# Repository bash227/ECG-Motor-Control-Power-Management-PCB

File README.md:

# ECG-Integrated Motor Control PCB  
**Final Project for BME405 - Introduction to Design of Medical Electronic Devices**  
*Ankara University, Department of Biomedical Engineering*  

---

## Project Overview  
A multi-functional PCB combining:  
- **ECG Signal Acquisition** (INA188 instrumentation amplifier, 0.5Hz-100Hz bandwidth)  
- **Power Management** (3.6V Li-ion charging, ±5V/12V regulation)  
- **Motor/Actuator Control** (BD6220F-E2 driver, relay circuits)  

---

## Team Members  
| Name              | Role                                  |  
|-------------------|---------------------------------------|  
| [bash227](https://github.com/bash227)| PCB Layout              |  
| [UmutAygun](https://github.com/UmutAygun)| Schematic Design          |  

---

## Repository Structure  
```plaintext
ECG_Motor_PCB/
├── Hardware/ 
│   │   
│   ├── Outputs/
│   └── 3D models/
├── Documentation/
└── README.md
```

## Key Features
### Power managment
- MCP73831 Li-ion charger (0.5A)
- TLV61070A boost converter (3.6V→5V)
- LMC7660 voltage inverter (+5V→-5V)

### ECG Frontend
- INA188 instrumentation amplifier (G=10)
- 0.05Hz high-pass filter
- 50Hz notch filter

### Motor Control
- BD6220F-E2 DC motor driver
- AP8803WTG-7 LED driver
- Optoisolated relay control
---
##  Setup Guide
1. Clone the repository:
```bash
git clone https://github.com/yourusername/ECG-Motor-Control-PCB.git
```
2. Open in KiCad:
```bash
PCB_FINAL_UPDATED.kicad_pro
```
3. Set 3D model path in KiCad:
```bash
KICAD8_3DMODEL_DIR = ${KIPRJMOD}/Hardware/3D_Models
```
## Academic Information
- Course: BME405 - Introduction to Medical Electronics Design
- Institution: Ankara University

## License

This project is licensed under the **MIT License** - see the [LICENSE](LICENSE) file for details.

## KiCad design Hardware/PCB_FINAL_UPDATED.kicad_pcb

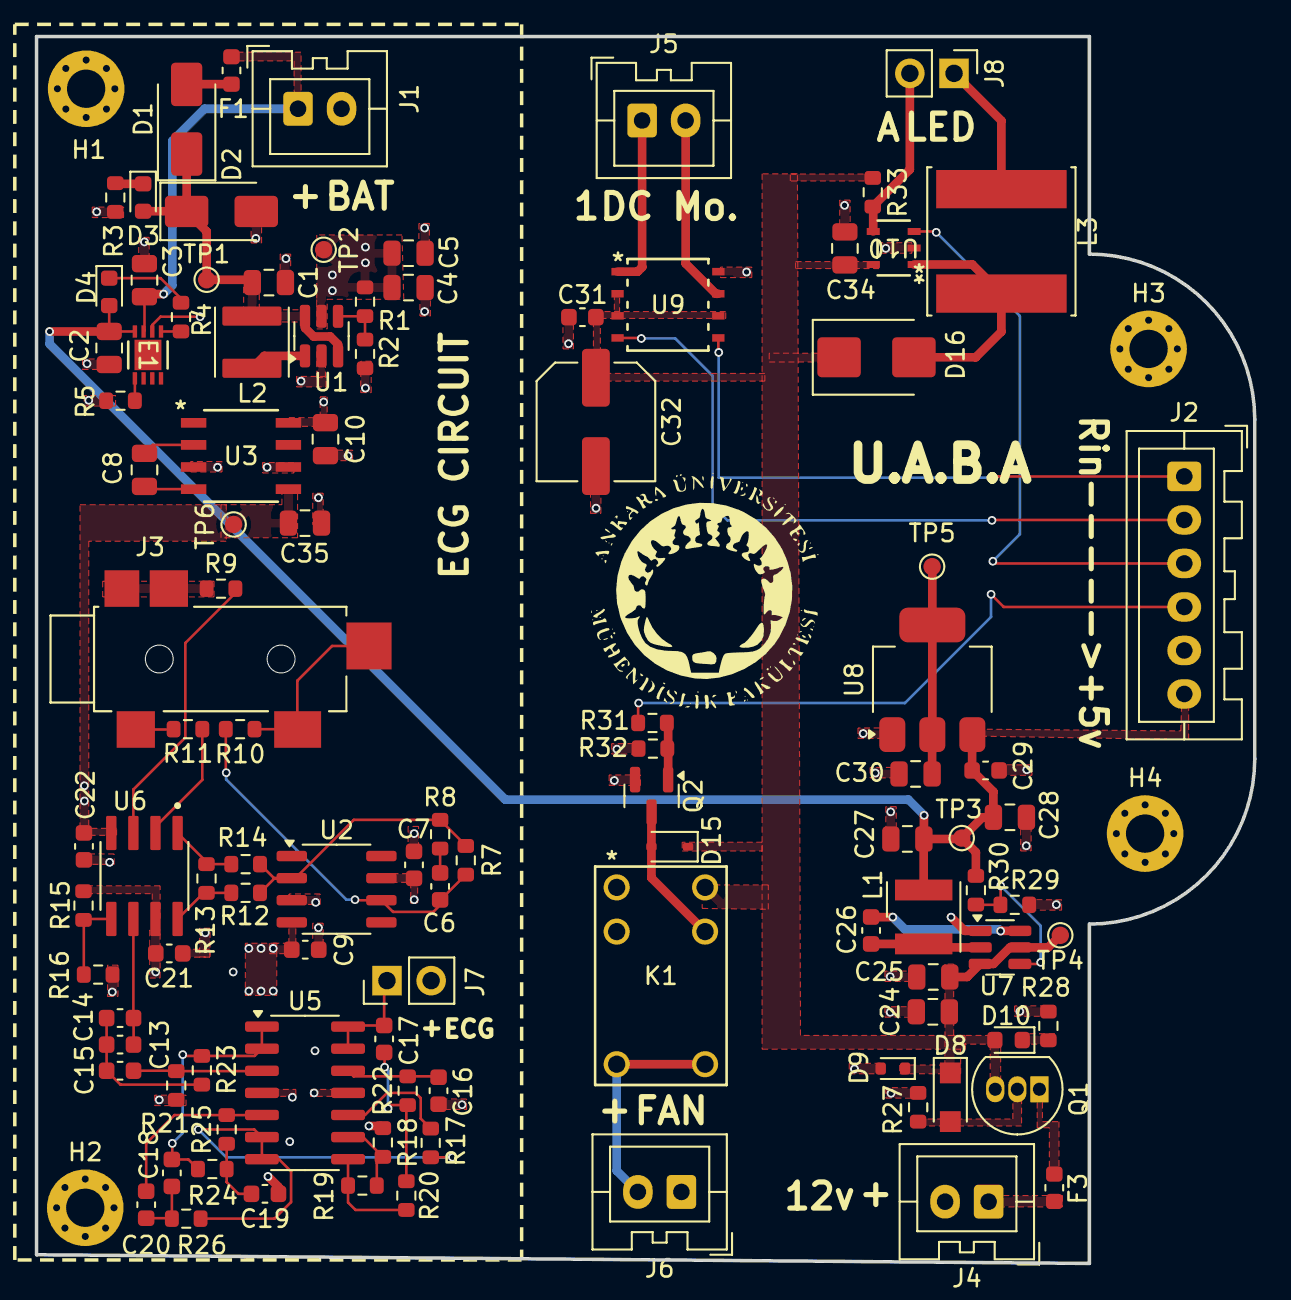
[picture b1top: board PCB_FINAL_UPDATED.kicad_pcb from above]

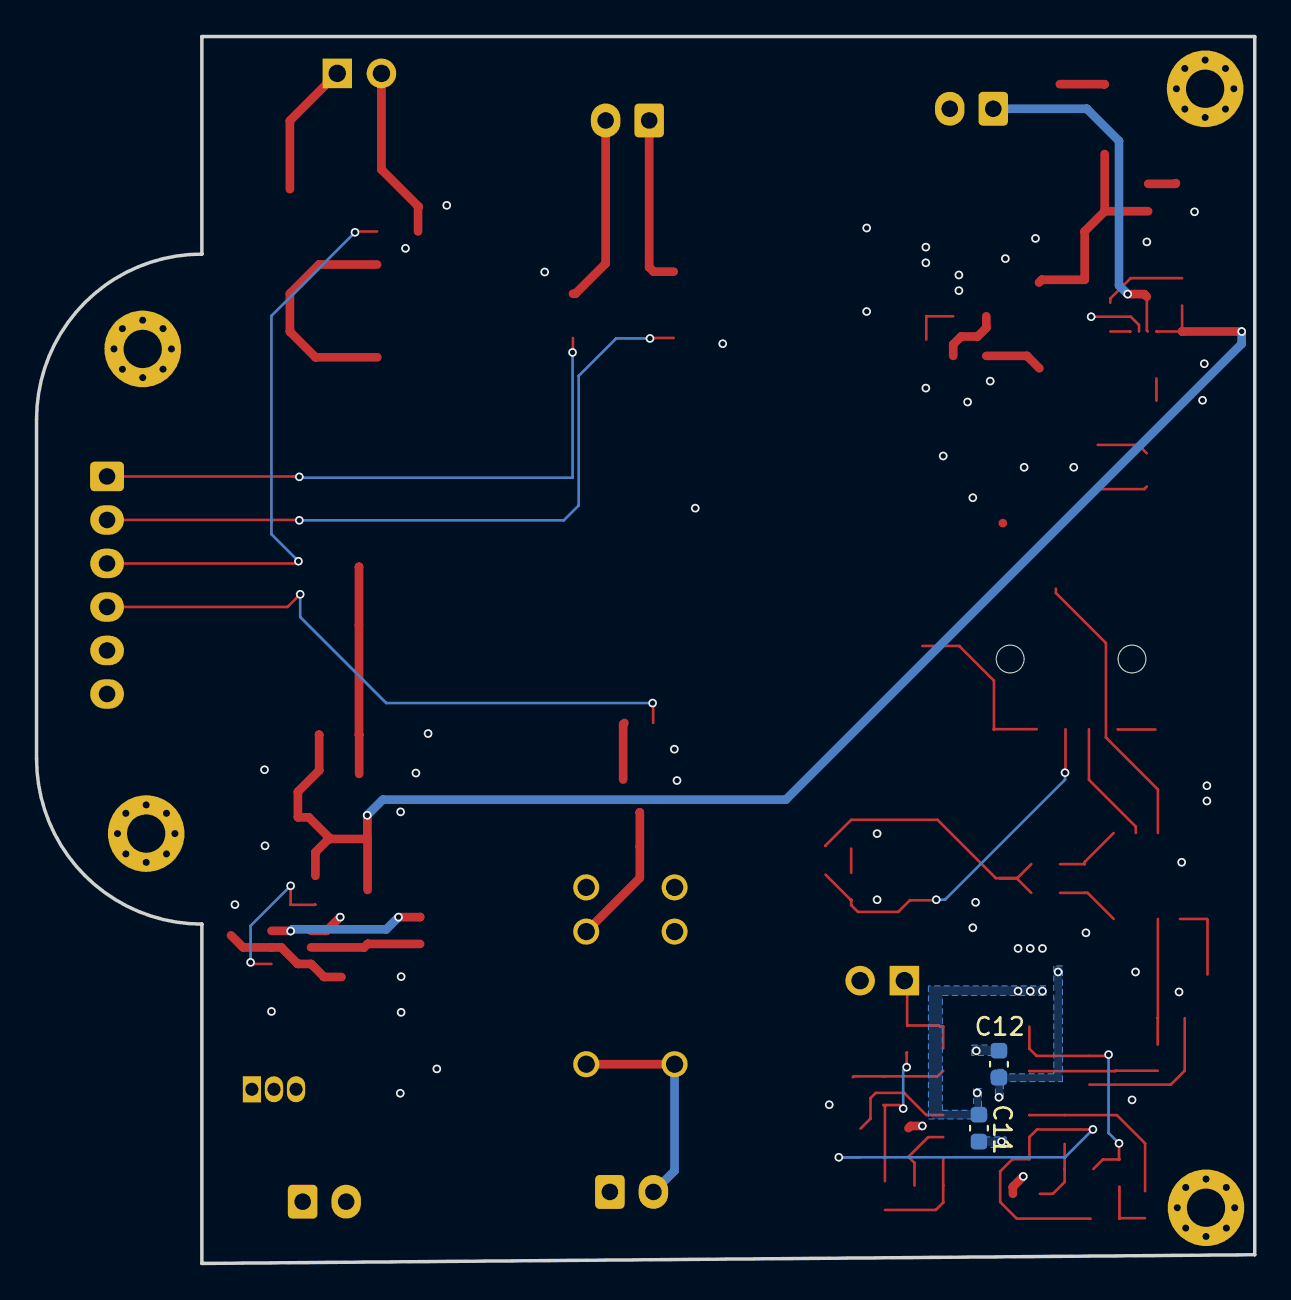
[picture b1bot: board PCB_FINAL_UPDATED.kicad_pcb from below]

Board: 4 copper layers, 70.0 x 70.5 mm, 110 parts (2 on the bottom side), 61 nets.

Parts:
C1, C4, C5, C27, C28: 22uF; C_0805_2012Metric
C2, C3, C34: 4.7uF; C_0805_2012Metric
C6, C7, C9, C11, C12, C21, C22, C26: 100nF; C_0603_1608Metric
C8, C10, C24, C25, C35: 10uF; C_0805_2012Metric
C13, C14: 10u; C_0603_1608Metric
C15: 470nF; C_0603_1608Metric
C16: 33n; C_0603_1608Metric
C17, C18, C20, C29, C31: 100n; C_0603_1608Metric
C19: 220nF; C_0603_1608Metric
C30: 10u; C_0805_2012Metric
C32: 220u; C_Elec_6.3x7.7
D1: SS36; D_SMA
D2: SMAJ5.0A; D_SMA
D3, D4, D10: YLED; LED_0603_1608Metric
D8: 10V; Nexperia_CFP3_SOD-123W
D9: 13V; D_SOD-523
D15: 1N4148WS; D_SOD-323
D16: B240; D_SMB
E1: MCP73831-2ACI/MC; DFN8_2x3MC_MCH-L
F1: 0.5 A; Fuse_0603_1608Metric
F3: 6A-24VDC; Fuse_0603_1608Metric
H1, H2, H3, H4: MountingHole_Pad; MountingHole_2.2mm_M2_Pad_Via
J1: 3.6 Li-ion battery; JST_XA_B02B-XASK-1_1x02_P2.50mm_Vertical
J2: Conn_01x06_Socket; JST_XA_B06B-XASK-1_1x06_P2.50mm_Vertical
J3: 35RASMT4BHNTRX
J4, J5, J6: Conn_01x02_Socket; JST_XA_B02B-XASK-1_1x02_P2.50mm_Vertical
J7, J8: Conn_01x02_Pin; PinHeader_1x02_P2.54mm_Vertical
K1: G5V-1 DC12; G5V_1
L1: 3.3 uH; L_Wurth_WE-LQSH-4020
L2: 3.3 uH; L_Abracon_ASPI-4030S
L3: 100uH; L_Changjiang_FNR8040S
Q1: BS108; TO-92_Inline
Q2: BC817; SOT-23
R1: 90.9k; R_0603_1608Metric
R2, R8, R18, R29: 10k; R_0603_1608Metric
R3, R16, R28, R31: 1k; R_0603_1608Metric
R4: 470; R_0603_1608Metric
R5: 2k; R_0603_1608Metric
R7, R19: 1M; R_0603_1608Metric
R9, R10, R11: 220k; R_0603_1608Metric
R12, R14: 22.6k; R_0603_1608Metric
R13: 6.98k; R_0603_1608Metric
R15, R27: 100k; R_0603_1608Metric
R17: 20k; R_0603_1608Metric
R20: 14.3k; R_0603_1608Metric
R21: 6.8M; R_0603_1608Metric
R22: 48.1k; R_0603_1608Metric
R23: 113k; R_0603_1608Metric
R24, R25: 30.9k; R_0603_1608Metric
R26: 16.9k; R_0603_1608Metric
R30: 53.6k; R_0603_1608Metric
R32: 10K; R_0603_1608Metric
R33: 100m; R_0603_1608Metric
TP1, TP2, TP3, TP4, TP5, TP6: TestPoint; TestPoint_Pad_D1.0mm
U1: TLV61070ADBV; SOT-23-6
U2: OP07; SO-8_3.9x4.9mm_P1.27mm
U3: LMC7660IMX; M08A_TEX
U5: TL084; SOIC-14_3.9x8.7mm_P1.27mm
U6: INA188ID
U7: TPS562201; SOT-23-6
U8: AMS1117-3.3; SOT-223-3_TabPin2
U9: BD6220F-E2; SOP8_ROM-L
U10: AP8803WTG-7; TSOT25-WT_DIO-L

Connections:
3.6V: C1.1, D1.1 (K), D2.1 (A1), D3.2 (A), L2.1, TP1.1, U1.3 (EN), U1.6 (V_{IN})
+3.3V: C30.1, TP5.1, U8.2 (VO)
+5V: C4.1, C5.1, C7.1, C10.2, C12.1, C21.1, R1.2, R15.2, TP2.1, U1.5 (V_{OUT}), U2.7 (V+), U3.8 (V+), U5.4 (V+), U6.7 (V+)
+5VA: C2.1, C27.1, C28.1, C29.1, D4.2 (A), E1.4, J2.6, L1.2, R30.2, TP3.1, U8.3 (VI)
+12V: C24.1, C25.1, C31.1, C32.1, C34.2, D8.1 (K), D9.1 (K), D10.2 (A), D15.1 (K), D16.1 (K), K1.2, K1.10, Q1.3 (S), R33.1, TP4.1, U7.3 (VIN), U7.5 (EN), U9.2 (VCC), U9.3 (VCC), U9.6 (VREF), U10.5 (VIN)
-5V: C9.1, C11.1, C22.1, C35.2, TP6.1, U2.4 (V-), U3.5 (OUT), U5.11 (V-), U6.4 (V-)
/ANALOG CIRCUIT/HPF_O: C18.1, R23.2, R24.1, U5.1, U5.2 (-)
/ANALOG CIRCUIT/IAF_O: C13.1, C14.1, U6.6 (OUT)
/ANALOG CIRCUIT/LA: R9.2, U6.3 (IN+)
/ANALOG CIRCUIT/MAO: R19.2, R20.1, U5.8
/ANALOG CIRCUIT/NFO: R17.1, R26.2, U5.6 (-), U5.7
/ANALOG CIRCUIT/RA: R11.2, U6.2 (IN-)
/ANALOG CIRCUIT/RG1: R13.2, R14.2, U6.1 (RG)
/ANALOG CIRCUIT/RG2: R12.1, R13.1, U6.8 (RG)
/ANALOG CIRCUIT/RLD: C6.1, R7.1, R10.2, U2.6
/ANALOG CIRCUIT/RLI: R7.2, R8.2, R12.2, R14.1, U2.2 (-)
ECG_I: C17.2, J7.1, U5.13 (-), U5.14
FAN_C: J2.4, R31.1
FIN: J2.2, U9.4 (FIN)
GND: C1.2, C2.2, C3.2, C4.2, C5.2, C7.2, C9.2, C10.1, C11.2, C12.2, C16.1, C19.1, C21.2, C22.2, C24.2, C25.2, C27.2, C28.2, C29.2, C30.2, C31.2, C32.2, C34.1, C35.1, D2.2 (A2), D9.2 (A), E1.2, H1.1, H2.1, H3.1, H4.1, J1.2, J2.5, J4.2, J6.1, J7.2, Q2.2 (E), R2.1, R3.2, R5.2, R16.2, R18.1, R21.1, R27.2, R28.2, R29.2, R32.2, U1.2 (GND), U2.3 (+), U3.3 (GND), U3.6 (LV), U7.1 (GND), U8.1 (GND), U9.8 (GND), U10.2 (GND)
LED_PWM: J2.3, U10.3 (CTRL)
unnamed: C6.2, R8.1
unnamed: C13.2, C14.2, C15.1, R23.1
unnamed: C17.1, R20.2, R22.1
unnamed: C18.2, C20.1, R26.1
unnamed: C19.2, R24.2, R25.1
unnamed: D1.2 (A), F1.2
unnamed: D3.1 (K), R3.1
unnamed: D4.1 (K), R4.1
unnamed: D8.2 (A), Q1.2 (G), R27.1
unnamed: D10.1 (K), R28.1
unnamed: D15.2 (A), K1.9, Q2.3 (C)
unnamed: D16.2 (A), L3.1, U10.1 (SW)
unnamed: E1.1, R4.2
unnamed: J3.1, R11.1
unnamed: J3.2, J3.4, R9.1
unnamed: J3.3, J3.5, R10.1
unnamed: F3.1, J4.1
unnamed: J6.2, K1.5, K1.6
unnamed: J8.1, L3.2
unnamed: J8.2, R33.2, U10.4 (SET)
unnamed: F3.2, Q1.1 (D)
unnamed: Q2.1 (B), R31.2, R32.1
unnamed: L2.2, U1.1 (SW)
unnamed: R1.1, R2.2, U1.4 (V_{FB})
unnamed: C8.1, U3.2 (C1+)
unnamed: C8.2, U3.4 (C1-)
unnamed: C15.2, R21.2, U5.3 (+)
unnamed: C20.2, R25.2, U5.5 (+)
unnamed: R17.2, U5.10 (+)
unnamed: R18.2, R19.1, U5.9 (-)
unnamed: C16.2, R22.2, U5.12 (+)
unnamed: R15.1, R16.1, U6.5 (REF)
unnamed: C26.1, L1.1, U7.2 (SW)
unnamed: C26.2, U7.6 (VBST)
unnamed: R29.1, R30.1, U7.4 (VFB)
OUT1: J5.1, U9.1 (OUT1)
OUT2: J5.2, U9.7 (OUT2)
PROG: E1.5, R5.1
RIN: J2.1, U9.5 (RIN)
VBAT: C3.1, E1.3, F1.1, J1.1

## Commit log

2025-03-29 added the project files
2025-03-29 edited readme file
2025-03-29 added tbe contributers username
2025-03-29 edited read me file
2025-05-05 corrected some info in the readme file
